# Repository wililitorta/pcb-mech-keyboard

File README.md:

# pcb-mech-keyboard
 pcb build for a big ass es-MX keyboard

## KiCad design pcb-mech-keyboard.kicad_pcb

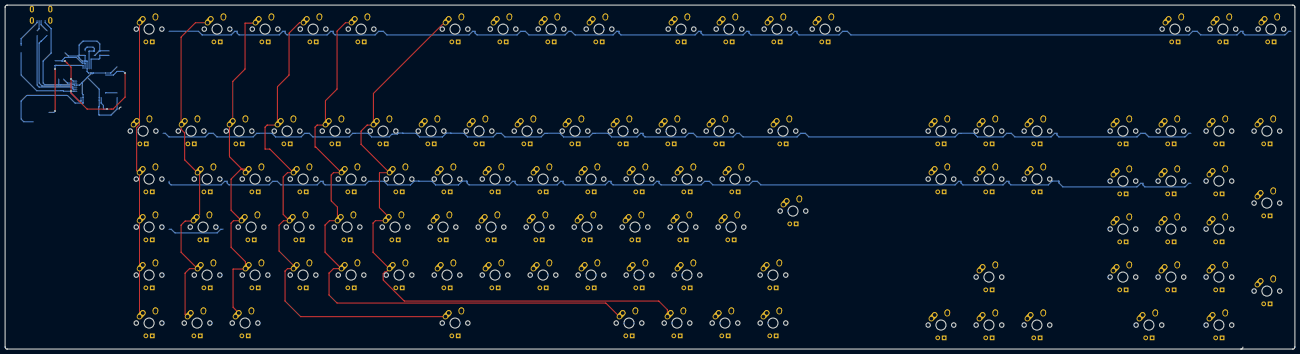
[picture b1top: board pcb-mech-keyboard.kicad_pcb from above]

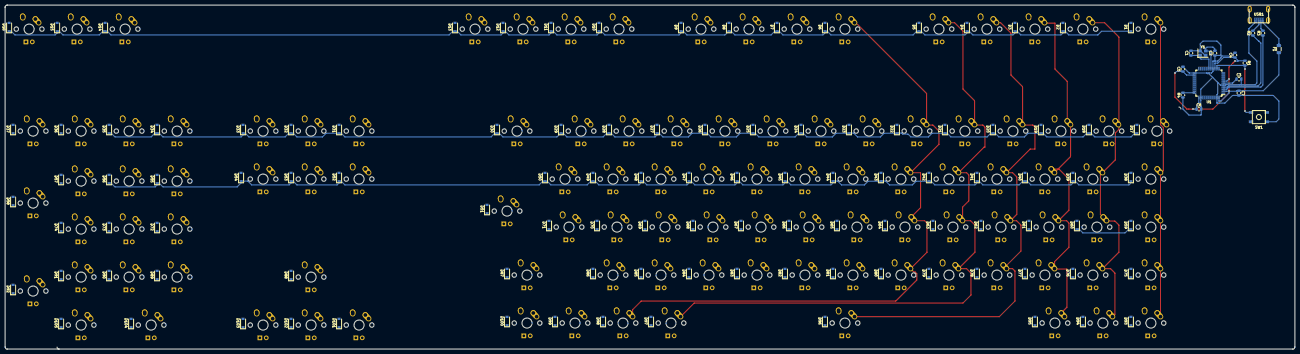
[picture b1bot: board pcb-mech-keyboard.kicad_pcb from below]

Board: 2 copper layers, 512.0 x 136.5 mm, 226 parts (121 on the bottom side), 142 nets.

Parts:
C1, C2: 22pF; C_0805_2012Metric
C3: 1uf; C_0805_2012Metric
C4, C5, C6: 0.1uF; C_0805_2012Metric
C7: 10uF; C_0805_2012Metric
D1, D2, D3, D4, D5, D6, D7, D8, D9, D10, D11, D12, D13, D14, D15, D16, D17, D18, D19, D20, D21, D22, D23, D24, D25, D26, D27, D28, D29, D30, D31, D32, D33, D34, D35, D36, D37, D38, D39, D40, D41, D42, D43, D44, D45, D46, D47, D48, D49, D50, D51, D52, D53, D54, D55, D56, D57, D58, D59, D60, D61, D62, D63, D64, D65, D66, D67, D68, D69, D70, D71, D72, D73, D74, D75, D76, D77, D78, D79, D80, D81, D82, D83, D84, D85, D86, D87, D88, D89, D90, D91, D92, D93, D94, D95, D96, D97, D98, D99, D100, D101, D102, D103, D104, D105: SOD-123; D_SOD-123
F1: 500mA; Fuse_1206_3216Metric
MX1, MX2, MX3, MX4, MX5, MX6, MX7, MX8, MX9, MX10, MX11, MX12, MX13, MX14, MX15, MX16, MX17, MX18, MX19, MX20, MX21, MX22, MX23, MX24, MX25, MX26, MX27, MX28, MX29, MX30, MX31, MX32, MX33, MX34, MX35, MX36, MX37, MX38, MX39, MX40, MX41, MX42, MX43, MX44, MX45, MX46, MX47, MX48, MX49, MX50, MX51, MX52, MX53, MX54, MX55, MX56, MX57, MX58, MX59, MX60, MX61, MX62, MX63, MX64, MX65, MX66, MX67, MX68, MX69, MX70, MX71, MX72, MX73, MX74, MX75, MX76, MX77, MX78, MX79, MX80, MX81, MX82, MX83, MX84, MX85, MX86, MX87, MX88, MX89, MX90, MX91, MX92, MX93, MX94, MX95, MX96, MX97, MX98, MX99, MX100, MX101, MX102, MX103, MX104, MX105: MX-NoLED; MX-1U
R1, R4: 10k; R_0805_2012Metric
R2, R3: 22; R_0805_2012Metric
SW1: SW_Push; SKQG-1155865
U1: ATmega32U4-AU; TQFP-44_10x10mm_P0.8mm
USB1: Molex-0548190589
Y1: 16MHz; Crystal_SMD_3225-4Pin_3.2x2.5mm

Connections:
+5V: C4.1, C5.1, C6.1, C7.1, F1.1, R1.1, U1.2, U1.7, U1.14, U1.24, U1.34, U1.44
COL0: MX1.1, MX17.1, MX38.1, MX59.1, MX75.1, MX93.1, U1.30
COL1: MX2.1, MX18.1, MX39.1, MX60.1, MX76.1, MX94.1, U1.12
COL2: MX3.1, MX19.1, MX40.1, MX61.1, MX77.1, MX95.1, U1.31
COL3: MX4.1, MX20.1, MX41.1, MX62.1, MX78.1, MX96.1, U1.32
COL4: MX5.1, MX21.1, MX42.1, MX63.1, MX79.1, MX97.1, U1.18
COL5: MX6.1, MX22.1, MX43.1, MX64.1, MX80.1, MX98.1, U1.19
COL6: MX7.1, MX23.1, MX44.1, MX65.1, MX81.1, MX99.1, U1.20
COL7: MX8.1, MX24.1, MX45.1, MX66.1, MX82.1, MX100.1, U1.21
COL8: MX9.1, MX25.1, MX46.1, MX67.1, MX83.1, MX101.1, U1.25
COL9: MX10.1, MX26.1, MX47.1, MX68.1, MX84.1, MX102.1, U1.22
COL10: MX11.1, MX27.1, MX48.1, MX69.1, MX85.1, MX103.1, U1.26
COL11: MX12.1, MX28.1, MX49.1, MX70.1, MX86.1, MX104.1, U1.27
COL12: MX13.1, MX29.1, MX50.1, MX71.1, MX87.1, MX105.1, U1.1
COL13: MX14.1, MX30.1, MX51.1, MX72.1, MX88.1, U1.41
COL14: MX15.1, MX31.1, MX52.1, MX73.1, MX89.1, U1.40
COL15: MX16.1, MX32.1, MX53.1, MX74.1, MX90.1, U1.39
COL16: MX33.1, MX36.1, MX54.1, MX57.1, MX91.1, U1.38
COL17: MX34.1, MX37.1, MX55.1, MX58.1, MX92.1, U1.37
COL18: MX35.1, MX56.1, U1.36
D+: R2.2, USB1.3
D-: R3.2, USB1.4
GND: C1.2, C2.1, C3.2, C4.2, C5.2, C6.2, C7.2, R4.1, SW1.1, U1.5, U1.15, U1.23, U1.35, U1.43, USB1.1, Y1.2, Y1.4
unnamed: C1.1, U1.17, Y1.1
unnamed: C2.2, U1.16, Y1.3
unnamed: C3.1, U1.6
unnamed: D1.2, MX1.2
unnamed: D2.2, MX2.2
unnamed: D3.2, MX3.2
unnamed: D4.2, MX4.2
unnamed: D5.2, MX5.2
unnamed: D6.2, MX6.2
unnamed: D7.2, MX7.2
unnamed: D8.2, MX8.2
unnamed: D9.2, MX9.2
unnamed: D10.2, MX10.2
unnamed: D11.2, MX11.2
unnamed: D12.2, MX12.2
unnamed: D13.2, MX13.2
unnamed: D14.2, MX14.2
unnamed: D15.2, MX15.2
unnamed: D16.2, MX16.2
unnamed: D17.2, MX17.2
unnamed: D18.2, MX18.2
unnamed: D19.2, MX19.2
unnamed: D20.2, MX20.2
unnamed: D21.2, MX21.2
unnamed: D22.2, MX22.2
unnamed: D23.2, MX23.2
unnamed: D24.2, MX24.2
unnamed: D25.2, MX25.2
unnamed: D26.2, MX26.2
unnamed: D27.2, MX27.2
unnamed: D28.2, MX28.2
unnamed: D29.2, MX29.2
unnamed: D30.2, MX30.2
unnamed: D31.2, MX31.2
unnamed: D32.2, MX32.2
unnamed: D33.2, MX33.2
unnamed: D34.2, MX34.2
unnamed: D35.2, MX35.2
unnamed: D36.2, MX36.2
unnamed: D37.2, MX37.2
unnamed: D38.2, MX38.2
unnamed: D39.2, MX39.2
unnamed: D40.2, MX40.2
unnamed: D41.2, MX41.2
unnamed: D42.2, MX42.2
unnamed: D43.2, MX43.2
unnamed: D44.2, MX44.2
unnamed: D45.2, MX45.2
unnamed: D46.2, MX46.2
unnamed: D47.2, MX47.2
unnamed: D48.2, MX48.2
unnamed: D49.2, MX49.2
unnamed: D50.2, MX50.2
unnamed: D51.2, MX51.2
unnamed: D52.2, MX52.2
unnamed: D53.2, MX53.2
unnamed: D54.2, MX54.2
unnamed: D55.2, MX55.2
unnamed: D56.2, MX56.2
unnamed: D57.2, MX57.2
unnamed: D58.2, MX58.2
unnamed: D59.2, MX59.2
unnamed: D60.2, MX60.2
unnamed: D61.2, MX61.2
unnamed: D62.2, MX62.2
unnamed: D63.2, MX63.2
unnamed: D64.2, MX64.2
unnamed: D65.2, MX65.2
unnamed: D66.2, MX66.2
unnamed: D67.2, MX67.2
unnamed: D68.2, MX68.2
unnamed: D69.2, MX69.2
unnamed: D70.2, MX70.2
unnamed: D71.2, MX71.2
unnamed: D72.2, MX72.2
unnamed: D73.2, MX73.2
unnamed: D74.2, MX74.2
unnamed: D75.2, MX75.2
unnamed: D76.2, MX76.2
unnamed: D77.2, MX77.2
unnamed: D78.2, MX78.2
unnamed: D79.2, MX79.2
unnamed: D80.2, MX80.2
unnamed: D81.2, MX81.2
unnamed: D82.2, MX82.2
unnamed: D83.2, MX83.2
unnamed: D84.2, MX84.2
unnamed: D85.2, MX85.2
unnamed: D86.2, MX86.2
unnamed: D87.2, MX87.2
unnamed: D88.2, MX88.2
unnamed: D89.2, MX89.2
unnamed: D90.2, MX90.2
unnamed: D91.2, MX91.2
unnamed: D92.2, MX92.2
unnamed: D93.2, MX93.2
unnamed: D94.2, MX94.2
unnamed: D95.2, MX95.2
unnamed: D96.2, MX96.2
unnamed: D97.2, MX97.2
unnamed: D98.2, MX98.2
unnamed: D99.2, MX99.2
unnamed: D100.2, MX100.2
unnamed: D101.2, MX101.2
unnamed: D102.2, MX102.2
unnamed: D103.2, MX103.2
unnamed: D104.2, MX104.2
unnamed: D105.2, MX105.2
unnamed: R1.2, SW1.2, U1.13
unnamed: R2.1, U1.4
unnamed: R3.1, U1.3
unnamed: R4.2, U1.33
ROW0: D1.1, D2.1, D3.1, D4.1, D5.1, D6.1, D7.1, D8.1, D9.1, D10.1, D11.1, D12.1, D13.1, D14.1, D15.1, D16.1, D36.1, D37.1, U1.8
ROW1: D17.1, D18.1, D19.1, D20.1, D21.1, D22.1, D23.1, D24.1, D25.1, D26.1, D27.1, D28.1, D29.1, D30.1, D31.1, D32.1, D33.1, D34.1, D35.1, U1.9
ROW2: D38.1, D39.1, D40.1, D41.1, D42.1, D43.1, D44.1, D45.1, D46.1, D47.1, D48.1, D49.1, D50.1, D51.1, D52.1, D53.1, D54.1, D55.1, D56.1, U1.10
ROW3: D57.1, D58.1, D59.1, D60.1, D61.1, D62.1, D63.1, D64.1, D65.1, D66.1, D67.1, D68.1, D69.1, D70.1, D71.1, D72.1, D73.1, D74.1, U1.11
ROW4: D75.1, D76.1, D77.1, D78.1, D79.1, D80.1, D81.1, D82.1, D83.1, D84.1, D85.1, D86.1, D87.1, D88.1, D89.1, D90.1, D91.1, D92.1, U1.28
ROW5: D93.1, D94.1, D95.1, D96.1, D97.1, D98.1, D99.1, D100.1, D101.1, D102.1, D103.1, D104.1, D105.1, U1.29
VCC: F1.2, USB1.5

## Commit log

2020-08-17 initialize project
2020-08-17 Add submodules
2020-08-17 Add footprint libraries
2020-08-17 Add schematics
2020-08-18 PCB built
